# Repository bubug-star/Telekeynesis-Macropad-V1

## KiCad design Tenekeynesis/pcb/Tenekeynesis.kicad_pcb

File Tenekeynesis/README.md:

# Tenekeynesis

> A compact 10-key ergonomic macropad powered by the Seeed XIAO RP2040 and KMK firmware.

---

## About

**Tenekeynesis** combines the words **Ten Keys** and **Telekinesis**.

This project is a custom-designed macropad created from scratch, including:

- Custom PCB designed in KiCad
- Custom ergonomic case designed in Tinkercad
- KMK firmware running on a Seeed XIAO RP2040
- Compact gaming-focused layout
- Single-piece printable enclosure

The goal was to create a simple but fully custom macropad while learning PCB design, CAD, firmware development, and hardware manufacturing workflows.

---

## Features

-  10-key gaming macropad
-  Direct GPIO wiring
-  Single-piece 3D printable case
-  Cherry MX compatible
-  Powered by KMK firmware
-  Compact 100 mm × 100 mm footprint
-  2.5° ergonomic tilt
-  Fully programmable keymap

---

# CAD Model

The case was designed entirely in **Tinkercad**.

The enclosure consists of a **single printed part** which integrates:

- PCB mounting surface
- Structural support
- Ergonomic typing angle
- Mounting locations for hardware

The design uses approximately **15 × 2.1 mm screws and nuts** for assembly.

---

## Case Render

---

# Electronics

The PCB was designed in **KiCad**.

The design intentionally avoids matrix scanning and instead uses direct GPIO connections for simplicity.

### Main Components

- Seeed XIAO RP2040
- 10 Cherry MX switches
- 10 DSA keycaps

---

## PCB Layout

---

## Schematic

---

# Firmware

Tenekeynesis uses **KMK Firmware** running on the XIAO RP2040.

The firmware is intentionally lightweight and easy to modify.

---

## Default Keymap

| Switch | Output |
|----------|----------|
| SW1 | W |
| SW2 | F |
| SW3 | S |
| SW4 | A |
| SW5 | Space |
| SW6 | V |
| SW7 | D |
| SW8 | E |
| SW9 | Q |
| SW10 | Tab |

---

# Bill of Materials

| Quantity | Component |
|-----------|-----------|
| 1 | Seeed XIAO RP2040 |
| 10 | Cherry MX Switches |
| 10 | DSA Keycaps |
| 15 | 2.1 mm Screws |
| 15 | 2.1 mm Nuts |
| 1 | Custom PCB |
| 1 | 3D Printed Case |

---

# Design Goals

The project was designed around several goals:

- Keep manufacturing simple
- Stay within the Hack Club size limits
- Learn PCB design from scratch
- Create a functional gaming macropad
- Maintain an ergonomic layout

---

# Development Journey

This project started with significantly more ambitious plans, including:

- TMR sensing
- Magnetic switches
- Analog input systems
- Custom switch mechanisms

As development progressed, the design was simplified to prioritize completion, manufacturability, and reliability.

The result is a complete custom macropad that can actually be built and used.

---

# Lessons Learned

Throughout the project I learned:

- KiCad schematic design
- PCB routing
- Manufacturing file generation
- CAD modelling
- Firmware development with KMK
- Hardware design workflows

This was my first complete keyboard-style hardware project.

---

# Future Plans

Tenekeynesis is only Version 1.

Future versions may include:

- Hall-effect switches
- TMR sensing
- Rapid Trigger
- Adjustable actuation points
- RGB lighting
- Additional layers and macros

---

# Gallery

## PCB

## Case

## Schematic

---

# Files

```
Tenekeynesis/
│
├── CAD/
│   └── Tenekeynesis.step
│
├── PCB/
│   ├── Tenekeynesis.kicad_pro
│   ├── Tenekeynesis.kicad_sch
│   └── Tenekeynesis.kicad_pcb
│
├── Firmware/
│   └── code.py
│
└── Production/
    ├── gerbers.zip
    └── code.py
```

---

## Extra Stuff

Building Tenekeynesis was quite an adventure.

What started as a simple macropad evolved into learning PCB design, firmware development, CAD modelling, manufacturing workflows, and hardware engineering.

This is only the beginning.

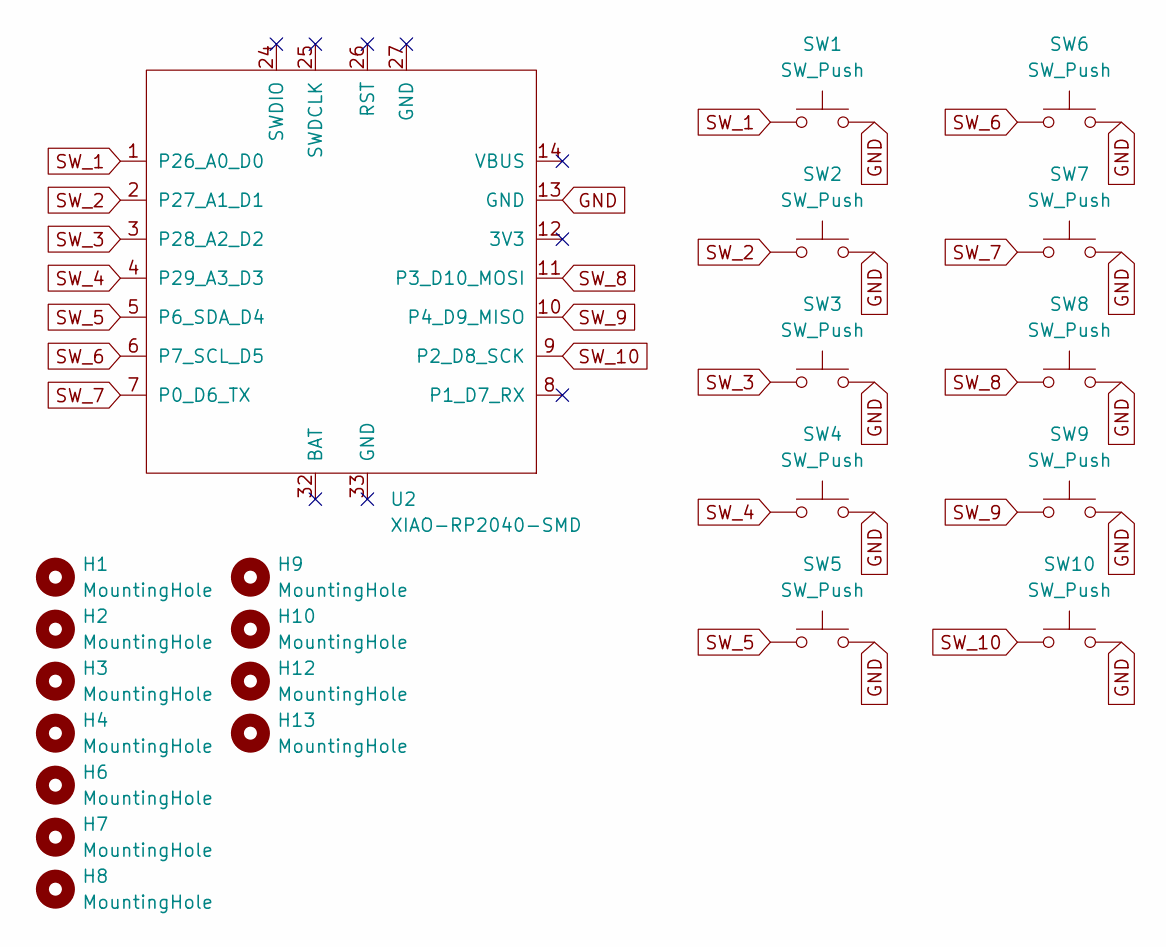
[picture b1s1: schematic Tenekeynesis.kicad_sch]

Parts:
H1, H2, H3, H4, H6, H7, H8, H9, H10, H12, H13: MountingHole; MountingHole_2.1mm
SW1, SW2, SW3, SW4, SW5, SW6, SW7, SW8, SW9, SW10: SW_Push; SW_Cherry_MX_1.00u_PCB
U2: XIAO-RP2040-SMD

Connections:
GND: SW1.2, SW2.2, SW3.2, SW4.2, SW5.2, SW6.2, SW7.2, SW8.2, SW9.2, SW10.2, U2.13 (GND)
SW_1: SW1.1, U2.1 (P26_A0_D0)
SW_2: SW2.1, U2.2 (P27_A1_D1)
SW_3: SW3.1, U2.3 (P28_A2_D2)
SW_4: SW4.1, U2.4 (P29_A3_D3)
SW_5: SW5.1, U2.5 (P6_SDA_D4)
SW_6: SW6.1, U2.6 (P7_SCL_D5)
SW_7: SW7.1, U2.7 (P0_D6_TX)
SW_8: SW8.1, U2.11 (P3_D10_MOSI)
SW_9: SW9.1, U2.10 (P4_D9_MISO)
SW_10: SW10.1, U2.9 (P2_D8_SCK)

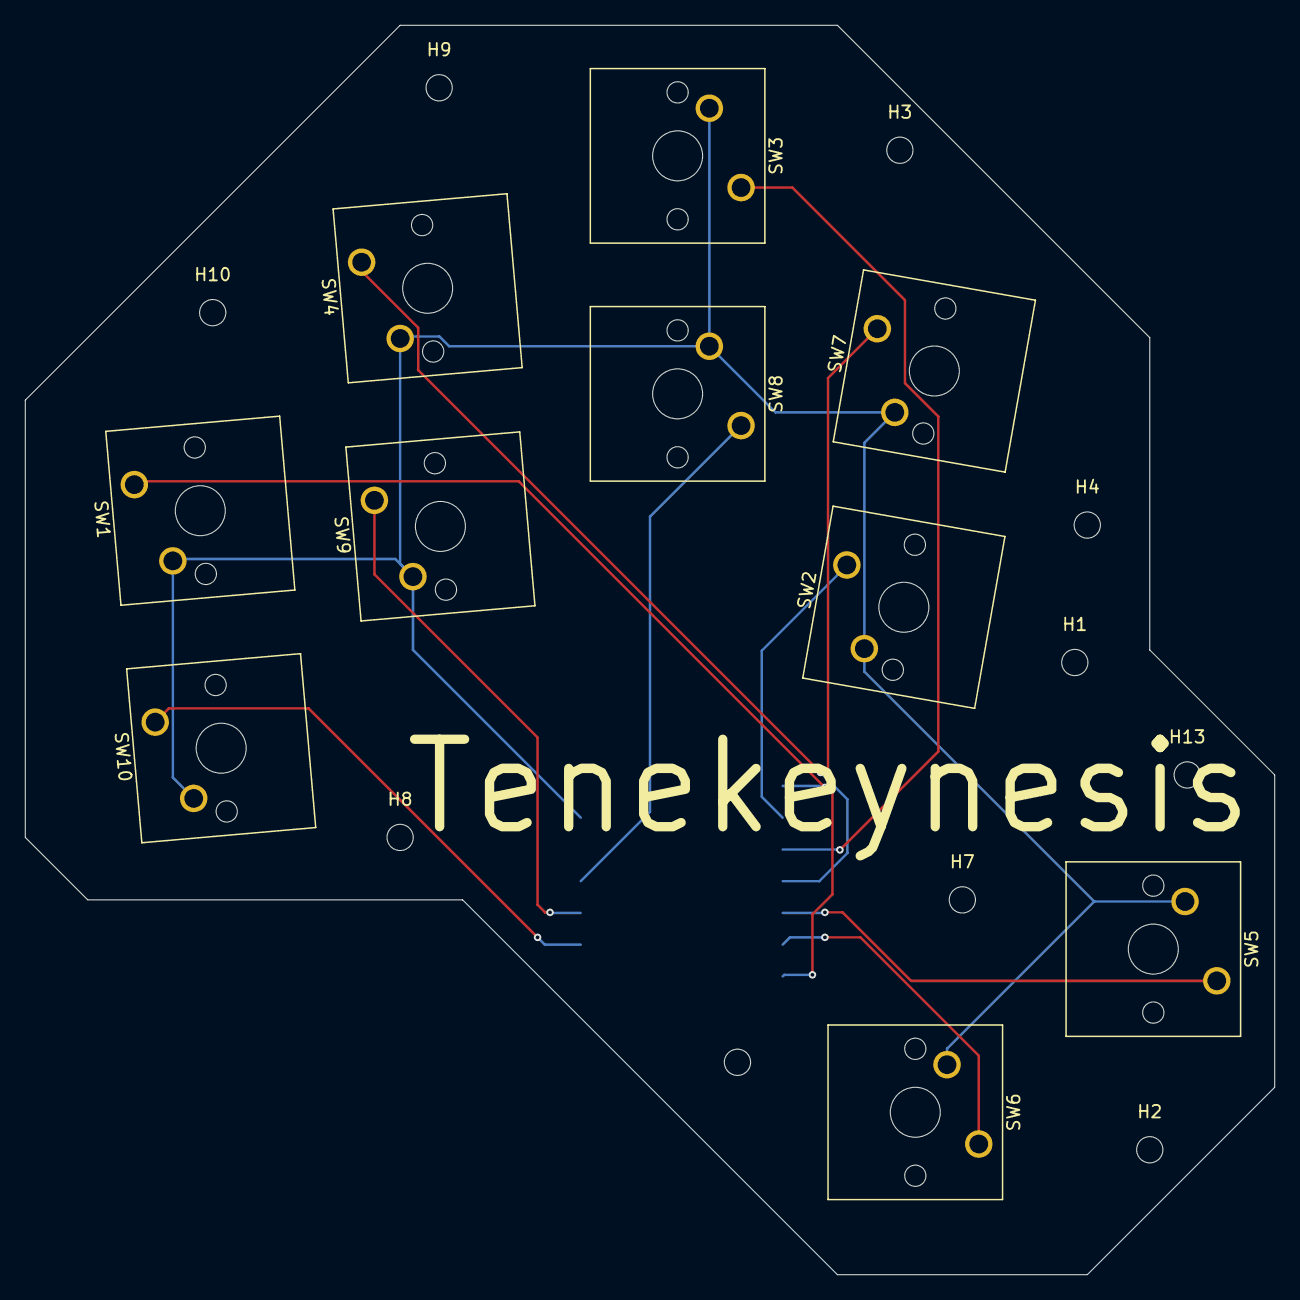
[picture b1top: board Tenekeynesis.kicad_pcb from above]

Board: 2 copper layers, 100.0 x 100.0 mm, 21 parts (1 on the bottom side), 11 nets.
